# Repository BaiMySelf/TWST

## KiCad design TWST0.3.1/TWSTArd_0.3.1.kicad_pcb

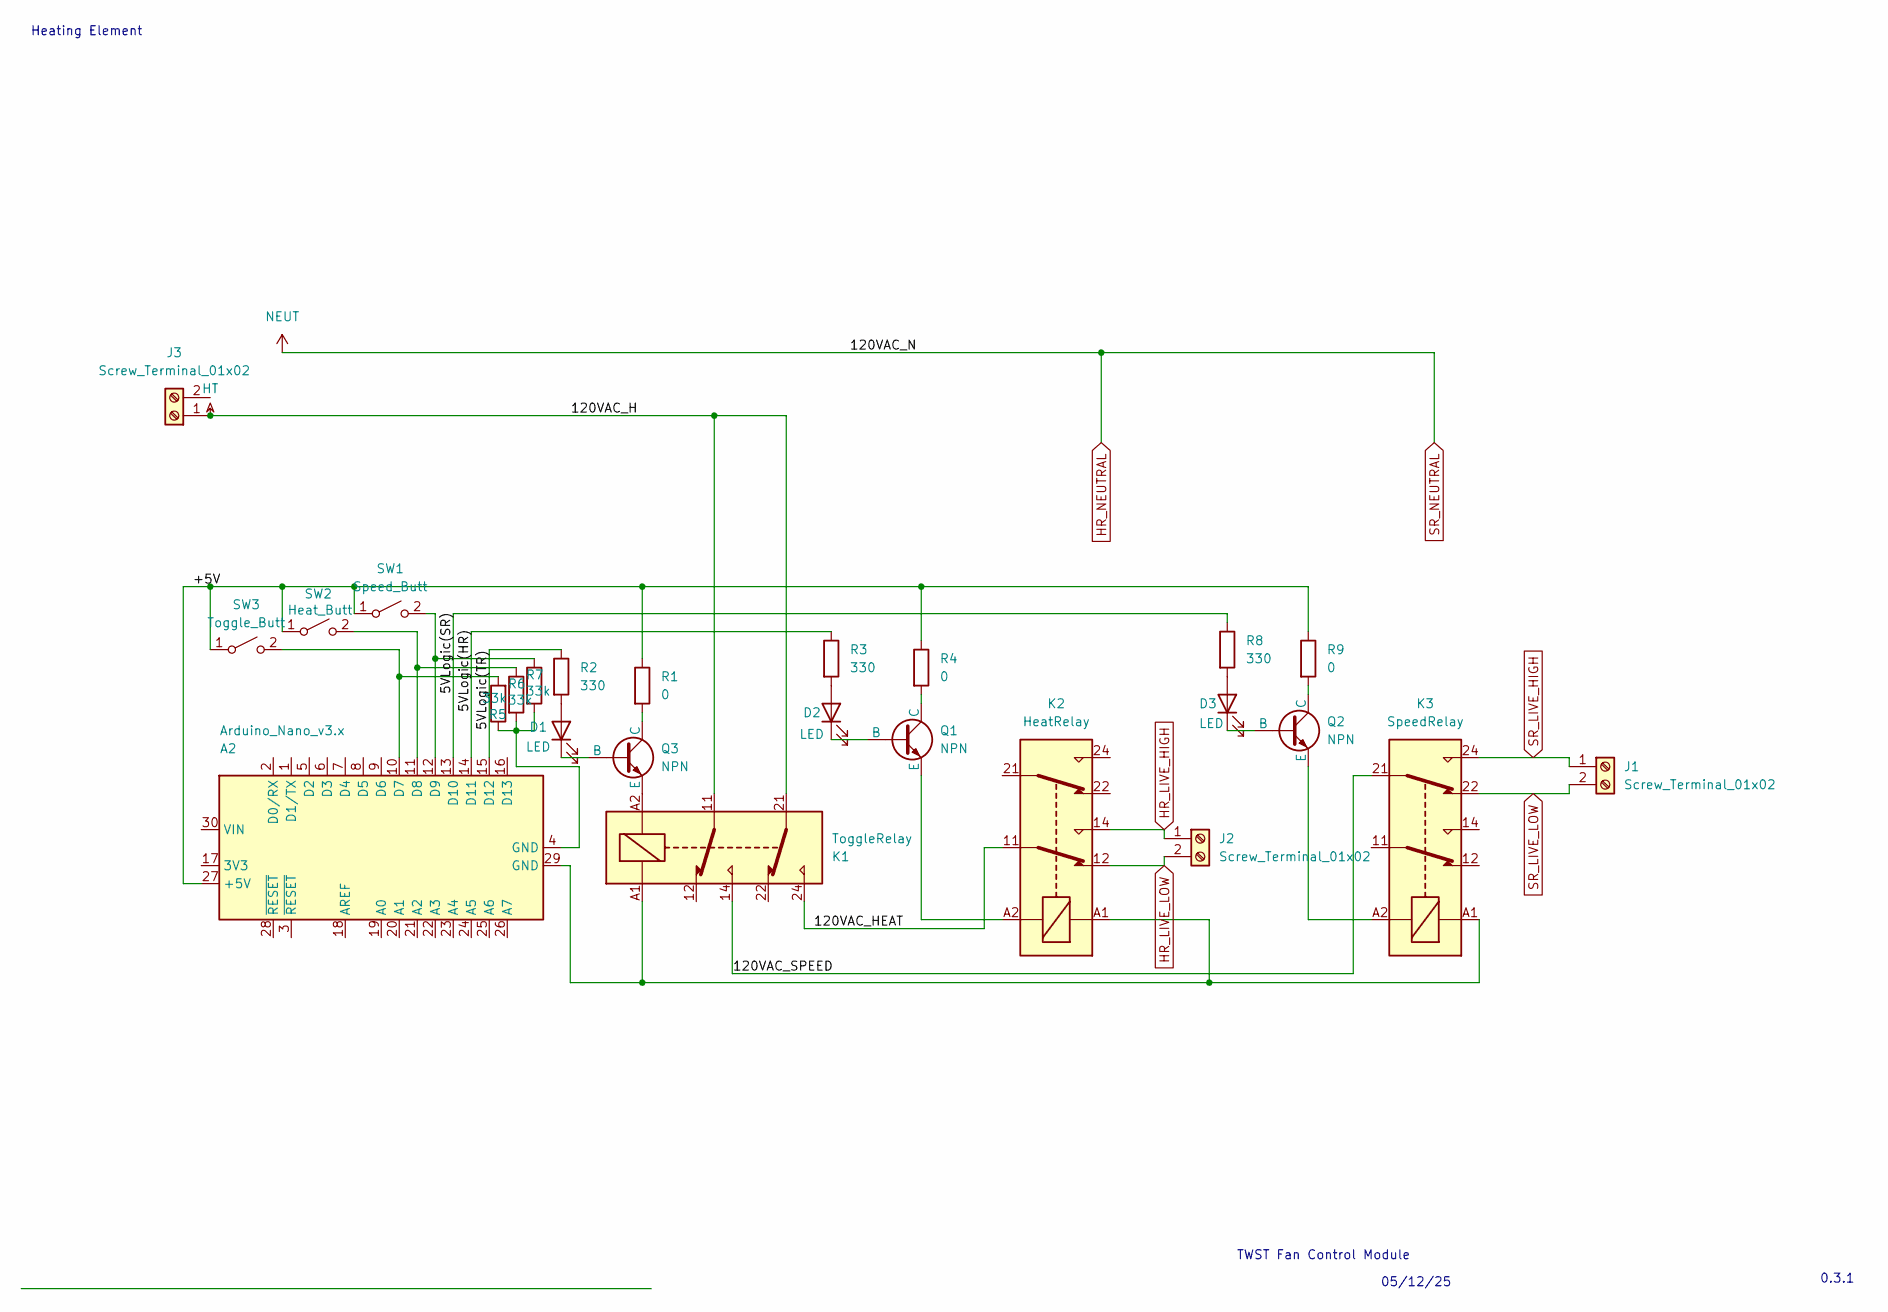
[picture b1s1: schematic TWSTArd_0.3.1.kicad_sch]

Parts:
A2: Arduino_Nano_v3.x; Arduino_Nano
D1, D2, D3: LED; LED_D3.0mm
J1, J2, J3: Screw_Terminal_01x02; TerminalBlock_bornier-2_P5.08mm
K1: ToggleRelay; Relay_DPDT_Schrack-RT2-FormC_RM5mm
K2: HeatRelay; Relay_DPDT_Schrack-RT2-FormC_RM5mm
K3: SpeedRelay; Relay_DPDT_Schrack-RT2-FormC_RM5mm
Q1, Q2, Q3: NPN; 2N3904
R1, R4, R9: 0; R_Axial_DIN0204_L3.6mm_D1.6mm_P5.08mm_Horizontal
R2, R3, R8: 330; R_Axial_DIN0204_L3.6mm_D1.6mm_P5.08mm_Horizontal
R5, R6, R7: 33k; R_Axial_DIN0204_L3.6mm_D1.6mm_P5.08mm_Horizontal
SW1: Speed_Butt; SW_PUSH_6mm_H4.3mm
SW2: Heat_Butt; SW_PUSH_6mm_H4.3mm
SW3: Toggle_Butt; SW_PUSH_6mm_H4.3mm

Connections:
/5VLogic(HR): A2.14 (D11), R3.1
/5VLogic(SR): A2.13 (D10), R8.1
/5VLogic(TR): A2.15 (D12), R2.1
/120VAC_HEAT: K1.24, K2.11
/120VAC_SPEED: K1.14, K3.21
/+5V: A2.27 (+5V), R1.1, R4.1, R9.1, SW1.1 (A), SW2.1 (A), SW3.1 (A)
HR_LIVE_HIGH: J2.1, K2.14
HR_LIVE_LOW: J2.2, K2.12
HT: J3.1, K1.11, K1.21
unnamed: A2.10 (D7), R5.2, SW3.2 (B)
unnamed: A2.11 (D8), R6.1, SW2.2 (B)
unnamed: A2.12 (D9), R7.1, SW1.2 (B)
unnamed: A2.4 (GND), R5.1, R6.2, R7.2
unnamed: A2.29 (GND), K1.A1, K2.A1, K3.A1
unnamed: D1.2 (A), R2.2
unnamed: D1.1 (K), Q3.2 (B)
unnamed: D2.2 (A), R3.2
unnamed: D2.1 (K), Q1.2 (B)
unnamed: D3.2 (A), R8.2
unnamed: D3.1 (K), Q2.2 (B)
unnamed: Q1.1 (C), R4.2
unnamed: K2.A2, Q1.3 (E)
unnamed: Q2.1 (C), R9.2
unnamed: K3.A2, Q2.3 (E)
unnamed: Q3.1 (C), R1.2
unnamed: K1.A2, Q3.3 (E)
SR_LIVE_HIGH: J1.1, K3.24
SR_LIVE_LOW: J1.2, K3.22

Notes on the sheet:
TWST Fan Control Module
0.3.1
05/12/25
Heating Element

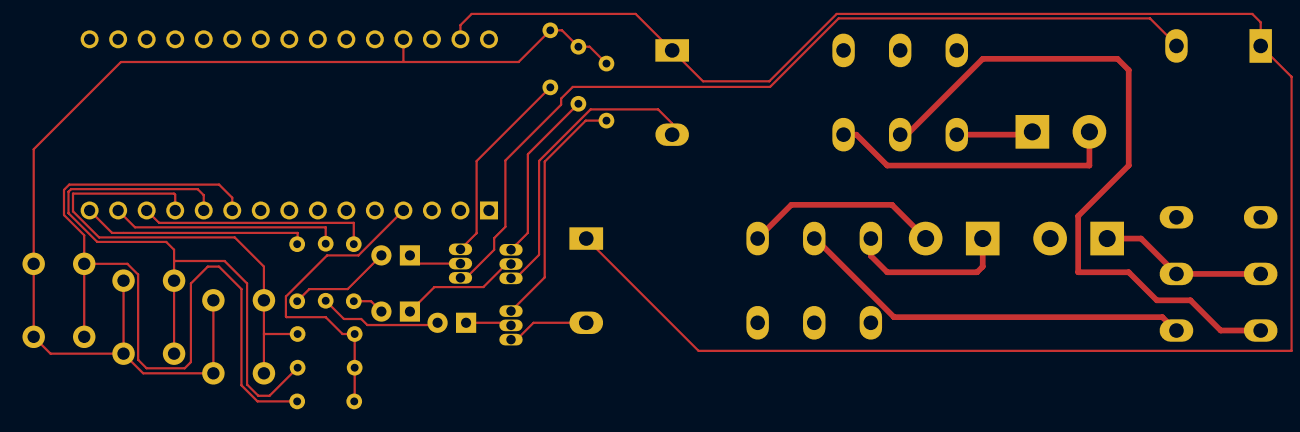
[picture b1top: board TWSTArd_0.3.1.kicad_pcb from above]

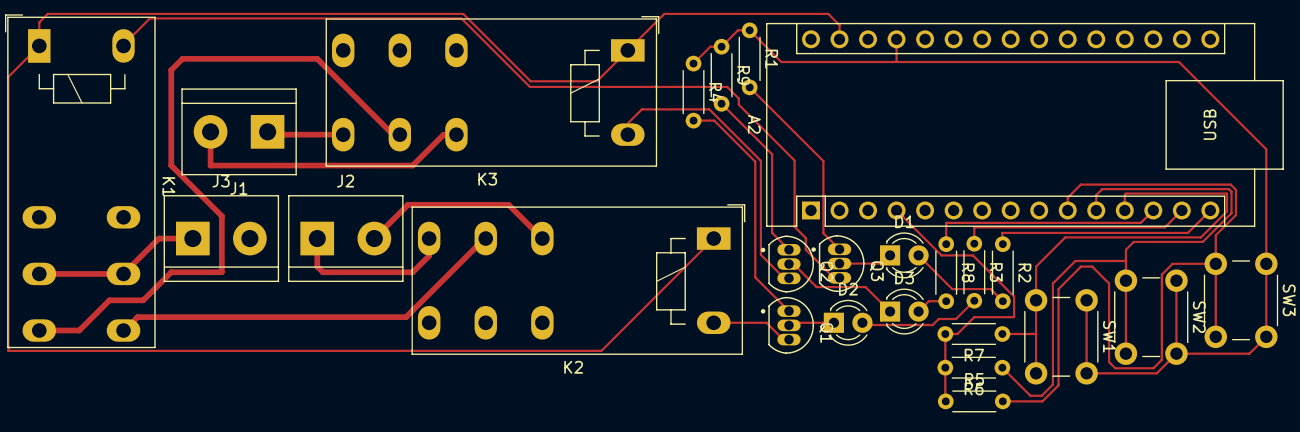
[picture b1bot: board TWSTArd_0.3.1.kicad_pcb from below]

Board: 2 copper layers, 25 parts (25 on the bottom side), 28 nets.

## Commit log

2024-11-30 Added the fan holder base.
    Initial alpha version of fan holder base.
2024-11-30 Added the TWST Baffle
    Initial alpha version of the TWST Baffle for use with the fan base.
2024-12-01 Modified clamp
    Remade mounting plate, added mounting holes, holes for M8 screws for clamp, started ductwork
2024-12-03 Fan Holder with mod for ducting
    Removed 90 degree duct, modified attachment to make the the interior slightly larger than 2 inches, increased total height of heating element shield to 16 cm for fit.
2024-12-05 Minor changes to spacing for printing
2024-12-05 Initial version of the concentrator
2025-05-14 TWST0.3.1 Files
2025-05-14 TWST0.3.1 Arudino Code
